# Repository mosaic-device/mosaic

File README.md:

# Mosaic

Mosaic is a connected desk display: an ESP32-P4 device, a .NET server it connects to, a web admin app for its owner, and a desktop companion.

Run every command from the repository root. Install the tools for the pieces you work on first: [setup](docs/setup.md) lists what each piece needs.

## Pieces

| Piece                                          | What it is                                                                   | Needs               | Run it                                        |
| ---------------------------------------------- | ---------------------------------------------------------------------------- | ------------------- | --------------------------------------------- |
| [Server](platform/apps/server/README.md)       | ASP.NET Core server: admin API, device WebSocket, serves the built admin app | .NET                | `pnpm server:dev`                             |
| [Admin](platform/apps/admin/README.md)         | React web app for the device owner                                           | Node, server        | `pnpm admin:dev`                              |
| [Companion](platform/apps/companion/README.md) | Tauri desktop app                                                            | Node, Rust/Tauri    | `pnpm companion:dev`                          |
| [Device preview](firmware/README.md#preview)   | The real firmware running in a window on your computer                       | Python, CMake, SDL2 | `pnpm fw:preview`                             |
| [Firmware](firmware/README.md#build-and-flash) | ESP32-P4 firmware for the Waveshare ESP32-P4-WIFI6-Touch-LCD-5               | ESP-IDF             | `pnpm fw:build`, then `pnpm fw:flash monitor` |
| [Carrier PCB](hardware/pcb/README.md)          | Board that connects the encoder, light sensor and LEDs to the header         | KiCad 10            | `pnpm pcb:export`                             |

The admin app expects the server on port 5000, so start `pnpm server:dev` in another terminal first. On first start the server logs a setup code; enter it on the admin app's setup page. Open the URL Vite prints.

Shared packages under `platform/packages/` hold the [device protocol](platform/packages/protocols/README.md), [design tokens](platform/packages/tokens/README.md) and [fonts, icons and sounds](platform/packages/assets/README.md).

## Check your changes

Pull requests run these checks; [CI](docs/ci.md) has the full list and how to reproduce each job.

| Area      | Fix formatting          | Check                                                               |
| --------- | ----------------------- | ------------------------------------------------------------------- |
| Web       | `pnpm web:format`       | `pnpm web:format:check`, `pnpm web:check`, `pnpm design:check`      |
| Server    | `pnpm server:format`    | `pnpm server:format:check`, `pnpm server:build`, `pnpm server:test` |
| Companion | `pnpm companion:format` | `pnpm companion:check`                                              |
| Firmware  | `pnpm fw:format`        | `pnpm fw:format:check`, `pnpm fw:test`, `pnpm fw:build`             |
| PCB       |                         | `pnpm pcb:check`                                                    |

`pnpm fw:test` runs every firmware host test on your computer, without ESP-IDF or a board. Pass part of a path to run only some: `pnpm fw:test provisioning clock`.

## Generated files

Do not hand-edit generated files.

- **Design tokens** are generated automatically by web builds and firmware builds. To generate them by hand, run `pnpm generate-tokens`.
- **Device protocol bindings** (C for the firmware, C# for the server) are committed, so builds don't need to generate them. After changing the schema, run `pnpm generate-protos` (needs access to `buf.build`) and commit the result. See [protocols](platform/packages/protocols/README.md).
- **Fonts, icons and sounds** are committed. Regenerate them only when their sources change; see [assets](platform/packages/assets/README.md#regenerate).

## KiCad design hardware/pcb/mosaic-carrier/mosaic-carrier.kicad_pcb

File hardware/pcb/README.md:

# Peripheral carrier PCB

A 30 × 70 mm, two-layer board that plugs onto pins 1–20 of the Waveshare ESP32-P4-WIFI6-Touch-LCD-5's 40-pin header and gives each peripheral its own latching JST-XH connector. It replaces the hand-wired perfboard prototype. The pin map comes from the [hardware wiki page](https://github.com/mosaic-device/mosaic/wiki/Hardware-Wiring-and-Power); the firmware needs no change.

The KiCad 10 project is in [`mosaic-carrier/`](mosaic-carrier/). Open `mosaic-carrier.kicad_pro` in KiCad to view or edit the schematic and layout.

## Fitting it

- **J1** is a male 2 × 10 header soldered on the **underside**, plastic against the board. JLCPCB doesn't fit it (see [Ordering](#ordering)); solder it yourself with the short pin ends through the board and the long ends pointing down. It plugs into the Waveshare's female socket at pins 1–20.
- Pin 1 (the square pad, marked `1` on the top) goes at the end of the Waveshare header nearest the corner mounting hole, with the 5V row nearest the board edge. The carrier then lies over the Waveshare board, running from the corner end toward its middle.
- Nothing else is on the underside, so it clears the parts beneath it.

## Connectors

Each cable is wired to its module at one end and a JST-XH housing at the other. The pin order follows each module's own pin order, so the wires don't cross.

| Connector    | Edge | Pins, from pin 1                               | Module pins                     |
| ------------ | ---- | ---------------------------------------------- | ------------------------------- |
| J2 Encoder   | Top  | GND, 3.3V, SW (GPIO2), DT (GPIO4), CLK (GPIO5) | KY-040: GND, +, SW, DT, CLK     |
| J3 Light     | Top  | SDA (GPIO21), SCL (GPIO22), GND, 3.3V          | GY-302: SDA, SCL, GND, VCC      |
| J4 LED ring  | Left | 5V, DIN (from GPIO28), GND                     | Ring: 5V, DIN, GND; DOUT unused |
| J5 LED strip | Left | 5V, DIN (from GPIO29), GND                     | Strip: 5V, DIN, GND             |

Pin 1 is marked with a triangle beside each connector. The GY-302's ADDR pin stays unconnected (address `0x23`). The speaker stays on the Waveshare board's own connector.

Crimp tools are optional: pre-crimped JST-XH leads with housings (3-, 4- and 5-pin) only need their bare ends soldered to the modules.

## Circuit

- **LED data** goes through a 74AHCT1G125 buffer powered from the LED 5V, so the LEDs get a full 5V signal. Three-pad solder jumpers JP1 (ring) and JP2 (strip) choose the path. The middle pad feeds the LED; it comes joined to the **BUF** pad by a thin copper link, so data goes through the buffer. To drive the LEDs straight from the GPIO, as on the prototype, cut that link with a knife and bridge the middle pad to the **GPIO** pad with solder. To go back, remove that solder and bridge the middle pad to **BUF** instead.
- **330 Ω** in each data line, at the board. It limits current into the first LED if its supply is missing and damps ringing on the cable; at 800 kHz it costs nothing in signal timing.
- **10 kΩ pull-downs** (R1, R2) hold the data lines low while the P4 boots, so the LEDs don't latch random colors.
- **F1**, a 1.1 A resettable fuse (1206, 0.8 mm tall), protects the header's 5V from a shorted LED cable. Firmware caps LED brightness at 30%, about 0.36 A for 8 + 12 LEDs. If it trips, the LEDs and their buffers go dark while the rest of the device keeps running; unplug, fix the short, and it reconnects on its own after about 30 seconds.
- **C1 and C5**, two 22 µF ceramics, sit across the LED supply. They are about 1.25 mm tall, so they fit where the board's edge is tight, and each LED has its own 100 nF beside it. A large electrolytic would only add height and a bigger surge from USB at plug-in.
- **I2C pull-ups** are on the GY-302 module, so the board has none. A sensor without its own needs 4.7 kΩ to 3.3V on SDA and SCL at the sensor end.
- The encoder needs no pull-ups on the board: the KY-040 has 10 kΩ on CLK, DT and SW.

## Check and export

```sh
pnpm pcb:check
pnpm pcb:export
```

`pcb:check` runs ERC and DRC (including schematic parity) and fails on any violation. `pcb:export` then writes `hardware/pcb/build/`, which is not committed:

| File                           | Use                                                                    |
| ------------------------------ | ---------------------------------------------------------------------- |
| `mosaic-carrier-gerbers.zip`   | Gerbers and drill files to upload to JLCPCB                            |
| `jlc-bom.csv`, `jlc-cpl.csv`   | BOM and placement for JLCPCB assembly                                  |
| `mosaic-carrier-schematic.pdf` | The schematic                                                          |
| `mosaic-carrier-assembly.html` | Where each part is and what it is, for probing and rework              |
| `mosaic-carrier.step`          | 3D model of the assembled board, for enclosure CAD; built locally only |

CI's **PCB** job runs the same export and uploads these files as an artifact, except the STEP model: CI's KiCad image has no component 3D models, so it skips it.

## Ordering

1. Upload the gerber zip with the default options (2 layers, 1.6 mm) and choose a **black** solder mask with white silkscreen.
2. Turn on assembly, choose **Economic PCBA** on the top side, and upload `jlc-bom.csv` and `jlc-cpl.csv`. Every part has an LCSC number. Both files leave out J1, the underside header: placing it would need Standard PCBA, which cost about four times as much for 5 boards.
3. In the placement preview, check each part's rotation, especially U1/U2 (pin 1 dot) and the JST connectors (opening toward the board edge). `jlc-cpl.csv` already corrects the buffers and JST connectors for JLCPCB's part models (`JLC_CORRECTIONS` in `scripts/pcb.py`), so they should need no adjustment; if a part still looks wrong, fix it in the preview and add or adjust its correction there.
4. Order J1 separately: any 2.54 mm 2 × 10 male header, such as LCSC C124359. Get a couple of spares.

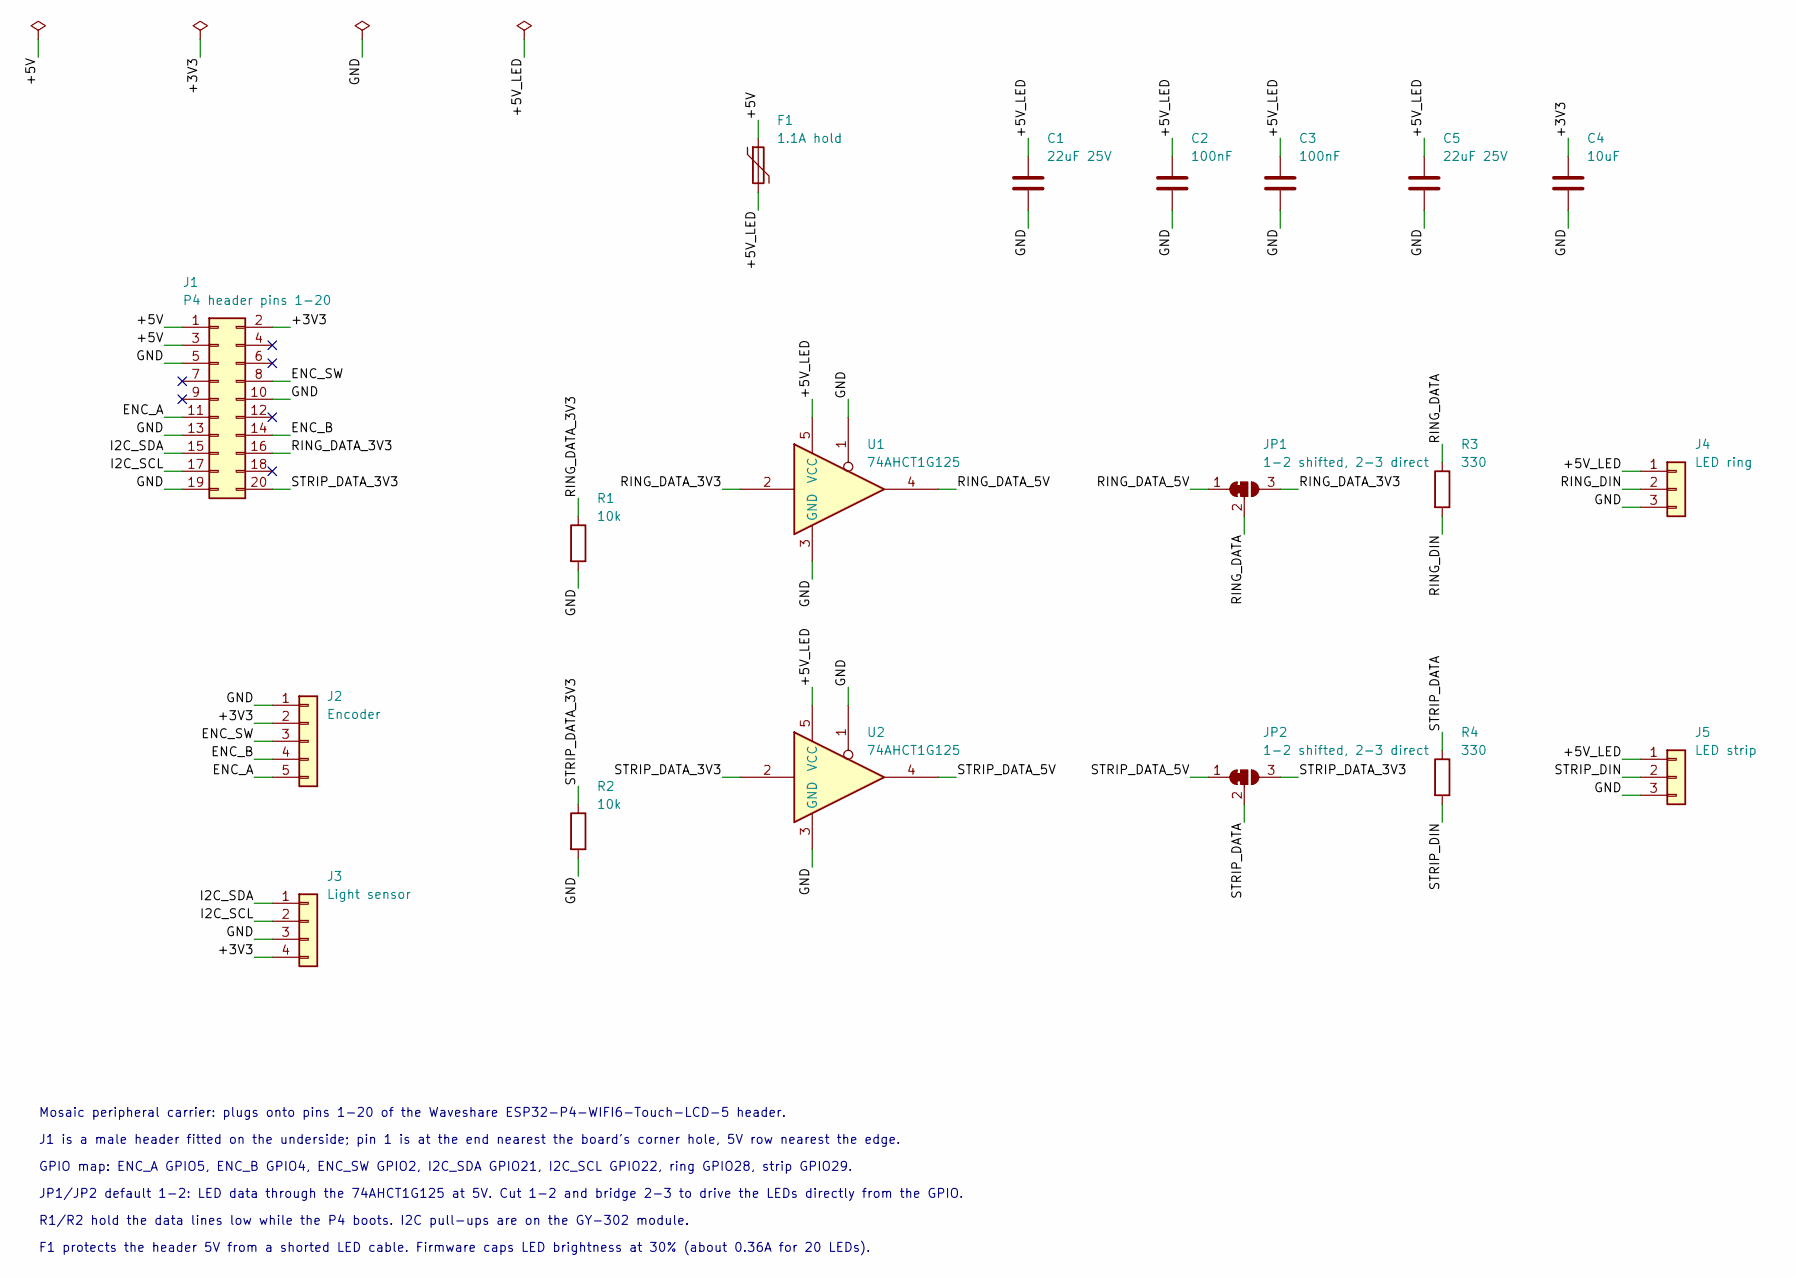
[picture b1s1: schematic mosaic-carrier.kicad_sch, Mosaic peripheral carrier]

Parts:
C1, C5: 22uF 25V; C_0805_2012Metric; LCSC C45783
C2, C3: 100nF; C_0603_1608Metric; LCSC C14663
C4: 10uF; C_0603_1608Metric; LCSC C19702
F1: 1.1A hold; Fuse_1206_3216Metric; LCSC C20801
J1: P4 header pins 1-20; PinHeader_2x10_P2.54mm_Vertical; LCSC C124359
J2: Encoder; JST_XH_S5B-XH-A-1_1x05_P2.50mm_Horizontal; LCSC C163038
J3: Light sensor; JST_XH_S4B-XH-A-1_1x04_P2.50mm_Horizontal; LCSC C163037
J4: LED ring; JST_XH_S3B-XH-A-1_1x03_P2.50mm_Horizontal; LCSC C163036
J5: LED strip; JST_XH_S3B-XH-A-1_1x03_P2.50mm_Horizontal; LCSC C163036
JP1, JP2: 1-2 shifted, 2-3 direct; SolderJumper-3_P1.3mm_Bridged12_RoundedPad1.0x1.5mm
R1, R2: 10k; R_0603_1608Metric; LCSC C25804
R3, R4: 330; R_0603_1608Metric; LCSC C23138
U1, U2: 74AHCT1G125; SOT-23-5; LCSC C7484

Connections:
/+3V3: C4.1, J1.2, J2.2, J3.4
/+5V: F1.1, J1.1, J1.3
/+5V_LED: C1.1, C2.1, C3.1, C5.1, F1.2, J4.1, J5.1, U1.5 (VCC), U2.5 (VCC)
/ENC_A: J1.11, J2.5
/ENC_B: J1.14, J2.4
/ENC_SW: J1.8, J2.3
/GND: C1.2, C2.2, C3.2, C4.2, C5.2, J1.5, J1.10, J1.13, J1.19, J2.1, J3.3, J4.3, J5.3, R1.2, R2.2, U1.1, U1.3 (GND), U2.1, U2.3 (GND)
/I2C_SCL: J1.17, J3.2
/I2C_SDA: J1.15, J3.1
/RING_DATA: JP1.2 (C), R3.1
/RING_DATA_3V3: J1.16, JP1.3 (B), R1.1, U1.2
/RING_DATA_5V: JP1.1 (A), U1.4
/RING_DIN: J4.2, R3.2
/STRIP_DATA: JP2.2 (C), R4.1
/STRIP_DATA_3V3: J1.20, JP2.3 (B), R2.1, U2.2
/STRIP_DATA_5V: JP2.1 (A), U2.4
/STRIP_DIN: J5.2, R4.2

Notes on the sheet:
Mosaic peripheral carrier: plugs onto pins 1-20 of the Waveshare ESP32-P4-WIFI6-Touch-LCD-5 header.
J1 is a male header fitted on the underside; pin 1 is at the end nearest the board's corner hole, 5V row nearest the edge.
GPIO map: ENC_A GPIO5, ENC_B GPIO4, ENC_SW GPIO2, I2C_SDA GPIO21, I2C_SCL GPIO22, ring GPIO28, strip GPIO29.
JP1/JP2 default 1-2: LED data through the 74AHCT1G125 at 5V. Cut 1-2 and bridge 2-3 to drive the LEDs directly from the GPIO.
R1/R2 hold the data lines low while the P4 boots. I2C pull-ups are on the GY-302 module.
F1 protects the header 5V from a shorted LED cable. Firmware caps LED brightness at 30% (about 0.36A for 20 LEDs).

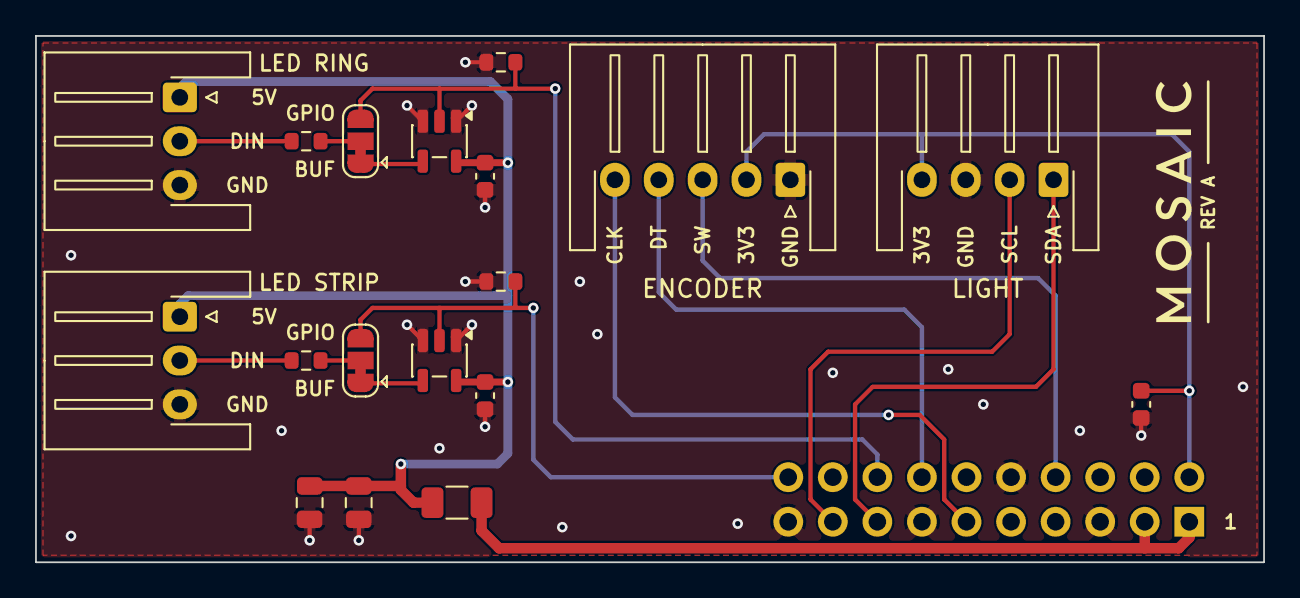
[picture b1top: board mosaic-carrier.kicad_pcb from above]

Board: 2 copper layers, 70.0 x 30.0 mm, 19 parts (1 on the bottom side), 17 nets.
